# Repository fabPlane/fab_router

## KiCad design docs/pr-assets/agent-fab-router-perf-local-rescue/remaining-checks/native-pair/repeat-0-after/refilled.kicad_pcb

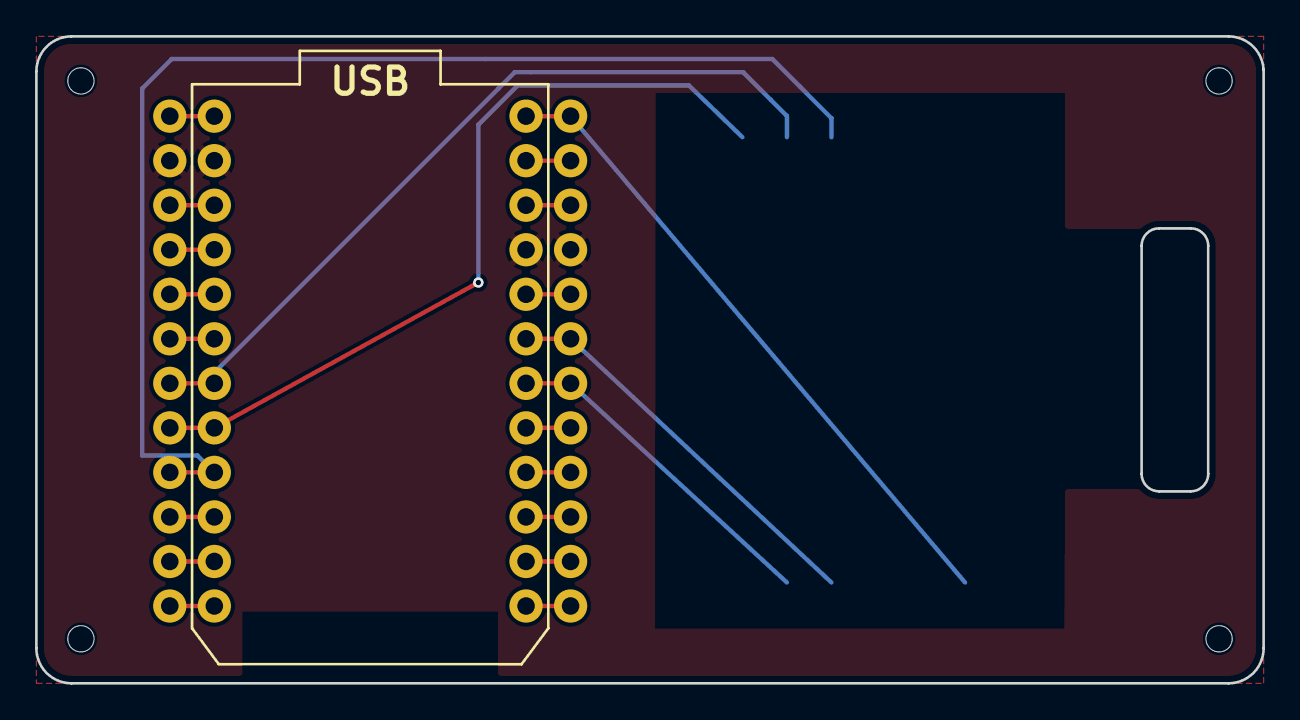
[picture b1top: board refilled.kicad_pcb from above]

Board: 2 copper layers, 70.0 x 36.9 mm, 6 parts (1 on the bottom side), 11 nets.

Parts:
A1: Photon; photon_headers
A2: paperino_module
M1, M2, M3, M4: Mounting_hole; mounting_hole_1.5

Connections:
+3V3: A1.24, A2.1
/INT1: A1.5, A2.6
/INT2: A1.18, A2.5
/SPI_CLK: A1.9, A2.9
/SPI_CS1: A1.10, A2.10
/SPI_CS2: A1.19, A2.4
/SPI_MISO: A1.8, A2.7
/SPI_MOSI: A1.7, A2.8
/~BUSY: A1.11, A2.12
/~RST: A1.12, A2.11
GND: A1.2, A1.21, A2.2

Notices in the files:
docs/pr-assets/agent-fab-router-perf-local-rescue/remaining-checks/native-pair/repeat-0-after/refilled.kicad_pcb:
licensed under CC-BY 4.0
